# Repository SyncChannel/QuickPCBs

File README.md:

# QuickPCBs
Simple and useful PCBs shared on The Sync Channel Blog

TCXO Breakout:
http://syncchannel.blogspot.com/2016/05/quick-pcb-tcxo-breakout.html

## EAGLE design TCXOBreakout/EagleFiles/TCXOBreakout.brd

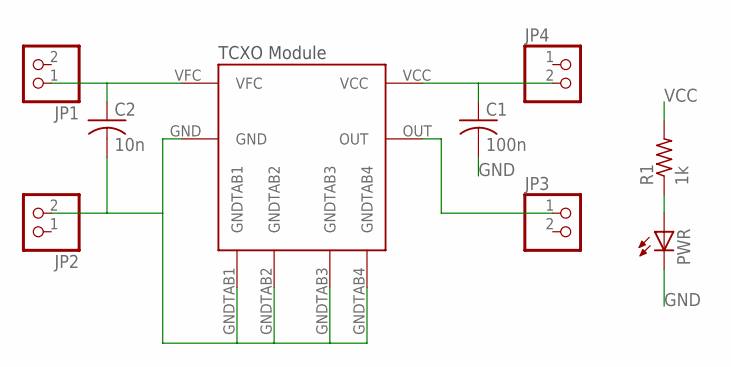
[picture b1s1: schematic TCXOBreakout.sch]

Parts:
C1: 100n; C0603
C2: 10n; C0603
JP1, JP2, JP3, JP4: PINHD-1X2; 1X02
PWR: LEDCHIPLED_0805; CHIPLED_0805
R1: 1k; R0603
U$1: TCXO2

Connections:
GND: C1.2, C2.2, JP2.2, PWR.C, U$1.GND, U$1.GNDTAB1, U$1.GNDTAB2, U$1.GNDTAB3, U$1.GNDTAB4
unnamed: PWR.A, R1.1
unnamed: C2.1, JP1.1, U$1.VFC
unnamed: JP3.1, U$1.OUT
VCC: C1.1, JP4.2, R1.2, U$1.VCC

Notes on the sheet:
TCXO Module

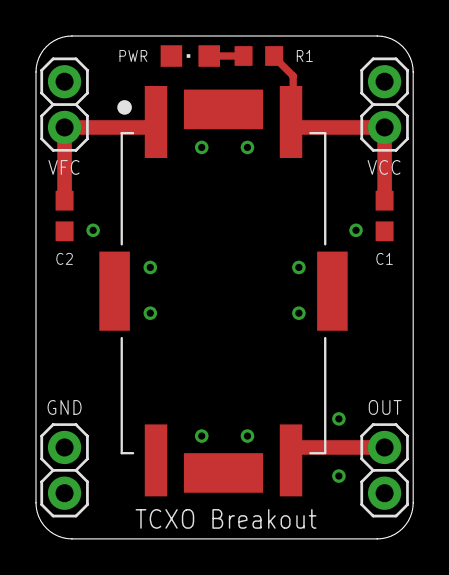
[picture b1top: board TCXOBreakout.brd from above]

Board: 2 copper layers, 21.0 x 27.9 mm, 9 parts (0 on the bottom side), 5 nets.

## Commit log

2016-05-15 :space_invader: Added .gitattributes & .gitignore files
2016-05-15 Added Eagle Files
2016-05-15 Added Readme
